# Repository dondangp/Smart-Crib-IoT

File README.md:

# Smart Crib IoT Abstract

The Smart Crib project integrates hardware and software components to provide users with a seamless and efficient smart home management solution. The system features smart lights, a smart door lock, and a smart fan, all of which can be controlled remotely through a user-friendly mobile application. The application serves as the central interface, allowing users to adjust light brightness, lock and unlock doors via a keypad or app controls, and set fan speeds. Communication between the app and devices is facilitated through an Azure Virtual Machine (VM) server, which processes HTTP control commands and maintains device statuses in real time.

The hardware layer includes an ESP32 microcontroller for the smart door lock & light and a Raspberry Pi Pico for the smart fan, enabling autonomous operations and network communication. The smart door lock features a keypad for local passcode input, providing an additional layer of security. The smart fan allows speed adjustments for customized comfort, while the smart lights support dynamic brightness levels for personalized lighting. By leveraging cloud-based infrastructure and efficient task management on microcontrollers, the Smart Crib project ensures reliable, responsive, and secure smart home control, blending convenience with cutting-edge IoT technology.

# Contributors
-  **Don Dang (Project Lead)**: Created the Smart Home React Native App and Final Poster. Scheduled meetings and assigned tasks for each individual and monitored who completed tasks and attended meetings.
-  **Luis Del Rio**: Created Azure VM server, Smart Light and Smart Doorlock devices. 
-  **Zait Martinez**: Created the hardware, software development, and Printed Circuit Board (PCB) for Smart Fan
- **Ethan Debnath**: Developed Software for IoT App
- **Pranav Pujar**: Developed Software for IoT App

*As of December 03, 2024 - This project will be wrapping up to a finish for Demo Day with no more commits to be made.*

## Features

- **Smart Lights**: Set the brightness of connected smart lights (0-100). Motion detection when someone walks nearby it will turn on the lights.
- **Smart Door Lock**: Lock or unlock the smart door with a simple toggle (Lock/Unlock). Keypad integration to unlock/lock the door lock.
- **Smart Fan**: Adjust the fan speed (Off, Cool, or Heat) to suit your comfort. Has a thermostat attached to it to indicate the degree in fahrenheit and also red and blue LED which will turn on to detect cool or heat mode of the fan.
- **Settings**: Settings to change the Smart Door Lock password.

## Built With

- **React Native**: A popular framework for building mobile applications using React.
- **Axios**: For making HTTP requests to the server.
- **@react-navigation**: For implementing tab-based navigation.
- **@expo/vector-icons**: For using Ionicons in the application.
- **ESP-32**: Smart light & lock hardware/software development
- **Raspberry Pi Pico**: Smart Fan & hardware/software development

# Prerequisites

Before you begin, ensure the following tools and dependencies are installed:

### 1. **Node.js**
   - Install Node.js to manage JavaScript runtime and packages.  
   [Download Node.js](https://nodejs.org/)

### 2. **Xcode**
   - Required for running React Native on iOS devices or emulators.  
   [Download Xcode](https://developer.apple.com/xcode/)

### 3. **npm or yarn**
   - Package managers installed along with Node.js for managing dependencies.

### 4. **Expo CLI**
   - To run the React Native application on mobile devices or emulators. Install via:
     ```bash
     npm install -g expo-cli
     ```

### 5. **Dependencies**
   - Install necessary packages:
     ```bash
     npm install
     npm install axios
     npx expo install expo@latest
     npx expo install --fix
     ```

### 6. **Network Requirement**
   - **Note**: UTA WiFi blocks React Native Expo. Use an alternative WiFi connection.

### 7. **C and Python 3.12.0+**
   - Ensure you have C Version C23 and Python 3.12.0 or higher installed for additional scripts or integrations.

## App Video Demos
[Smart Light & Lock Demo](https://www.youtube.com/watch?v=xLqYLixEVfE)

[Smart Fan Demo](https://www.youtube.com/shorts/cb8d_wNGdIk)

[Final Demo](https://youtu.be/l44uO0imUA0?si=sPAH7cayEWo_ZzFX)

## Demo Images
### Smart Fan Printed Circuit Board

### Smart Fan

### Smart Door Lock Front

### Smart Door Lock Keypad

### Smart Light (Off)

### Smart Light (On)

### Smart Fan Final Printed Circuit Board

### Smart Fan Back Layout

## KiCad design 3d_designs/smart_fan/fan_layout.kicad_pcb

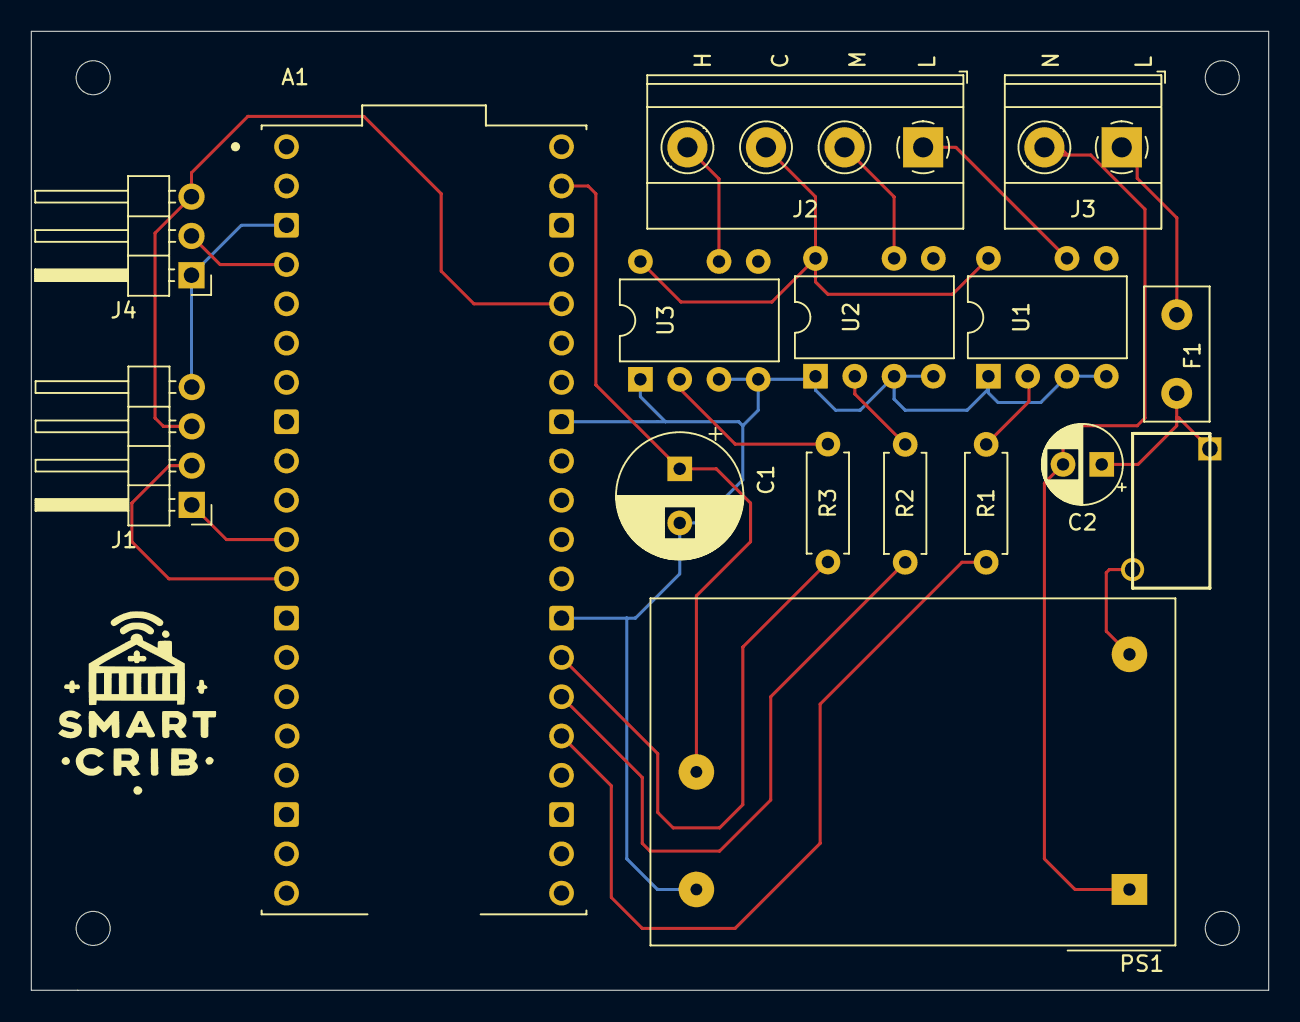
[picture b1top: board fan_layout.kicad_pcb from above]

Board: 2 copper layers, 80.0 x 62.0 mm, 16 parts (0 on the bottom side), 21 nets.

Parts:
A1: SC0918; MODULE_SC0918
C1: 470 uF; CP_Radial_D8.0mm_P3.50mm
C2: 0.1 uF; CP_Radial_D5.0mm_P2.50mm
F1: 1 A; Fuse_Littelfuse_395Series
J1: 01x04 Mount For Display; PinHeader_1x04_P2.54mm_Horizontal
J2: Fan mount for speed; TerminalBlock_Phoenix_MKDS-1,5-4-5.08_1x04_P5.08mm_Horizont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
J3: Terminal Block for AC input; TerminalBlock_Phoenix_MKDS-1,5-2_1x02_P5.00mm_Horizontal
J4: 01x03 Mount DHT; PinHeader_1x03_P2.54mm_Horizontal
PS1: IRM-02-5; Converter_ACDC_MeanWell_IRM-02-xx_THT
R1, R2, R3: 220; R_Axial_DIN0207_L6.3mm_D2.5mm_P7.62mm_Horizontal
RT1: SL15_30004; SL1530004
U1, U2, U3: AQH0213; DIP-8-N7_W7.62mm

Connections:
/AC-Live: F1.1, J3.1
/AC-Neutral: C2.2, J3.2, PS1.1 (AC/N)
/Common: J2.3, U1.8, U2.8, U3.8
/GND: A1.3 (GND), J1.4, J4.1
/High-Speed: J2.4, U3.6
/Low-Speed: J2.1, U1.6
/Medium-Speed: J2.2, U2.6
/Out: A1.4 (GP2), J4.2
/SCK: A1.12 (GP9), J1.2
/SDA: A1.11 (GP8), J1.1
/VCC: A1.36 (3V3_OUT), J1.3, J4.3
unnamed: A1.28 (GND), A1.33 (AGND), C1.2, PS1.3 (-Vo), U1.1, U1.3, U1.4, U2.1, U2.3, U2.4, U3.1, U3.3, U3.4
unnamed: A1.25 (GP19), R1.1
unnamed: A1.26 (GP20), R2.1
unnamed: A1.27 (GP21), R3.1
unnamed: A1.39 (VSYS), C1.1, PS1.4 (+Vo)
unnamed: C2.1, F1.2, RT1.1
unnamed: PS1.2 (AC/L), RT1.2
unnamed: R1.2, U1.2
unnamed: R2.2, U2.2
unnamed: R3.2, U3.2

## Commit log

2024-07-23 completed automated light proof of concept.
2024-07-28 updated folder
2024-07-28 SmartCrib React Native set up
2024-07-28 added .gitignore file to ignore large files like node_modules
2024-07-28 SmartCrib App Set Up, added .gitignore to ignore large files like node_modules
2024-07-28 added button and simplified ui
2024-07-30 new ui
2024-09-22 Rename .App.jsx.swp to .App.jsx
2024-10-01 updated UI
2024-10-01 Connected the react-native app to the smart lights, doorlock, and fan through http requests.
2024-10-03 Rename temperature.py to smartfan.py
2024-10-03 Updated features - smart lights brightness ranging from 0 to 100 and smart fan has four settings: off, low, medium, or high.
2024-10-03 headerfile for the smart doorlock keypad
2024-10-03 Example for how to use the keypad on the smart doorlock
2024-11-14 Styling the doorlock keypad
2024-11-14 Added keypad with clear, and send to server functionality with the door lock
2024-11-19 Connecting smart fan to the server
2024-11-19 Abstract Update
2024-11-19 Updated styles for door lock tab, settings page, and smart fan tab
2024-11-19 Refactor DoorlockScreen to add Lock and Unlock buttons and improve usability
    - Removed keypad for passcode entry in DoorlockScreen
    - Added TextInput for passcode entry
    - Implemented "Lock" and "Unlock" buttons with respective actions
    - Updated styles for Lock and Unlock buttons for distinct colors
    - Ensured passcode is cleared after performing lock/unlock actions
    - Simplified user interaction for door locking functionality
2024-11-19 removed keypad.h
2024-11-19 moved keypad_test.ino inside arduino folder
2024-11-19 Moved smartlight.ino into arduino folder
2024-11-19 Moved files around for better organization
2024-11-19 Smart Fan README.md update
2024-11-19 Adding settings to the features tab
2024-11-29 updated title
2024-11-29 Removed final demo
2024-11-29 Added contributors to Smart Home
2024-11-29 Updated contributors format
2024-11-29 Updated Demo Description
2024-11-29 updated .gitignore
2024-11-29 fixed .gitignore
2024-11-29 updated folder name to be more accurate
2024-11-29 updated SmartCrib to smart_home
2024-11-29 Updated Luis Colaborators
2024-11-29 added motion detection
2024-11-29 Changed name back to Smart Crib
2024-11-29 Removed motion detection in app
2024-11-29 updated smart_home back to smart_crib dir
2024-11-29 Working Basic Light Function
2024-11-29 working Keypad Thread
2024-11-29 Deleted password for lock/unlock
2024-11-29 Settings screen, implemented password is too long for new password
2024-11-30 Fixed the error of sending a string json value to an expected int for newPassword
2024-12-01 updated contributions
2024-12-01 Updated Smart Fan component status
2024-12-02 smart fan updated for heat and cool
2024-12-02 added more instructions to set up react native app
2024-12-02 updated smartfan.py to handle the server json data
2024-12-02 Uploaded printed circuit board demo
2024-12-02 demo config
2024-12-02 singlet hread
2024-12-03 implemented red/blue led for cool and heat
2024-12-03 Added video placeholder for final demo
2024-12-03 smart light feature update
2024-12-03 updated smart fan features
2024-12-03 Demo Images Update
2024-12-03 smart fan demo image
2024-12-03 front door lock demo image
2024-12-03 door lock keypad demo image
2024-12-03 smart light off demo image
2024-12-03 smart light on demo image
2024-12-03 project contributors update
2024-12-03 Smart fan PCB
2024-12-03 smart fan
2024-12-03 Smart Door Lock Front
2024-12-03 Smart Door Lock Keypad
2024-12-03 Smart Light Turned Off
2024-12-03 Smart Light Turned On
2024-12-03 Wrap up
2024-12-03 Fixing formatting issue
2024-12-03 Wrap up update
2024-12-03 final demo link added
2024-12-03 smart fan final pcb
2024-12-03 smart fan pcb final image
2024-12-03 fixing smart images
2024-12-03 prerequisites update
2024-12-03 App Video Demos
2024-12-03 updated luis contributes
2024-12-04 smart fan layout
2024-12-07 documentation
2024-12-07 smart fan designs
2024-12-08 3d_designs
2024-12-08 3d designs moved to appropriate area
